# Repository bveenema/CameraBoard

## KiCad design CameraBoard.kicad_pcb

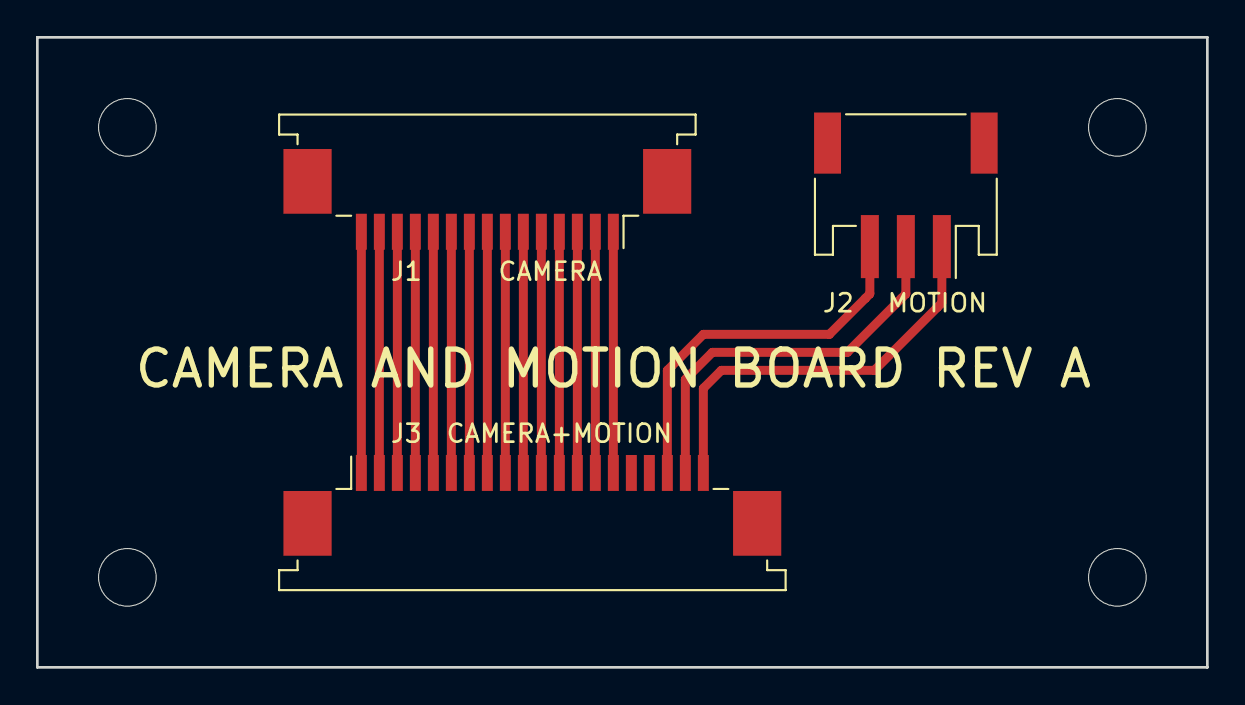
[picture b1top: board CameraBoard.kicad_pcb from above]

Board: 2 copper layers, 65.0 x 35.0 mm, 3 parts (0 on the bottom side), 18 nets.

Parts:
J1: CAMERA; TE_1-84953-5_1x15_P1.0mm_Horizontal
J2: MOTION; JST_PH_S3B-PH-SM4-TB_03x2.00mm_Angled
J3: CAMERA+MOTION; TE_2-84953-0_1x20_P1.0mm_Horizontal

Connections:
unnamed: J1.1, J3.15
unnamed: J1.2, J3.14
unnamed: J1.3, J3.13
unnamed: J1.4, J3.12
unnamed: J1.5, J3.11
unnamed: J1.6, J3.10
unnamed: J1.7, J3.9
unnamed: J1.8, J3.8
unnamed: J1.9, J3.7
unnamed: J1.10, J3.6
unnamed: J1.11, J3.5
unnamed: J1.12, J3.4
unnamed: J1.13, J3.3
unnamed: J1.14, J3.2
unnamed: J1.15, J3.1
unnamed: J2.1, J3.20
unnamed: J2.2, J3.19
unnamed: J2.3, J3.18

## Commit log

2018-05-07 Rev A
2018-05-07 Create Schematic PDF Rev A
2018-05-07 Rename Schematic Rev A
2018-05-08 PCB smaller Rev A
